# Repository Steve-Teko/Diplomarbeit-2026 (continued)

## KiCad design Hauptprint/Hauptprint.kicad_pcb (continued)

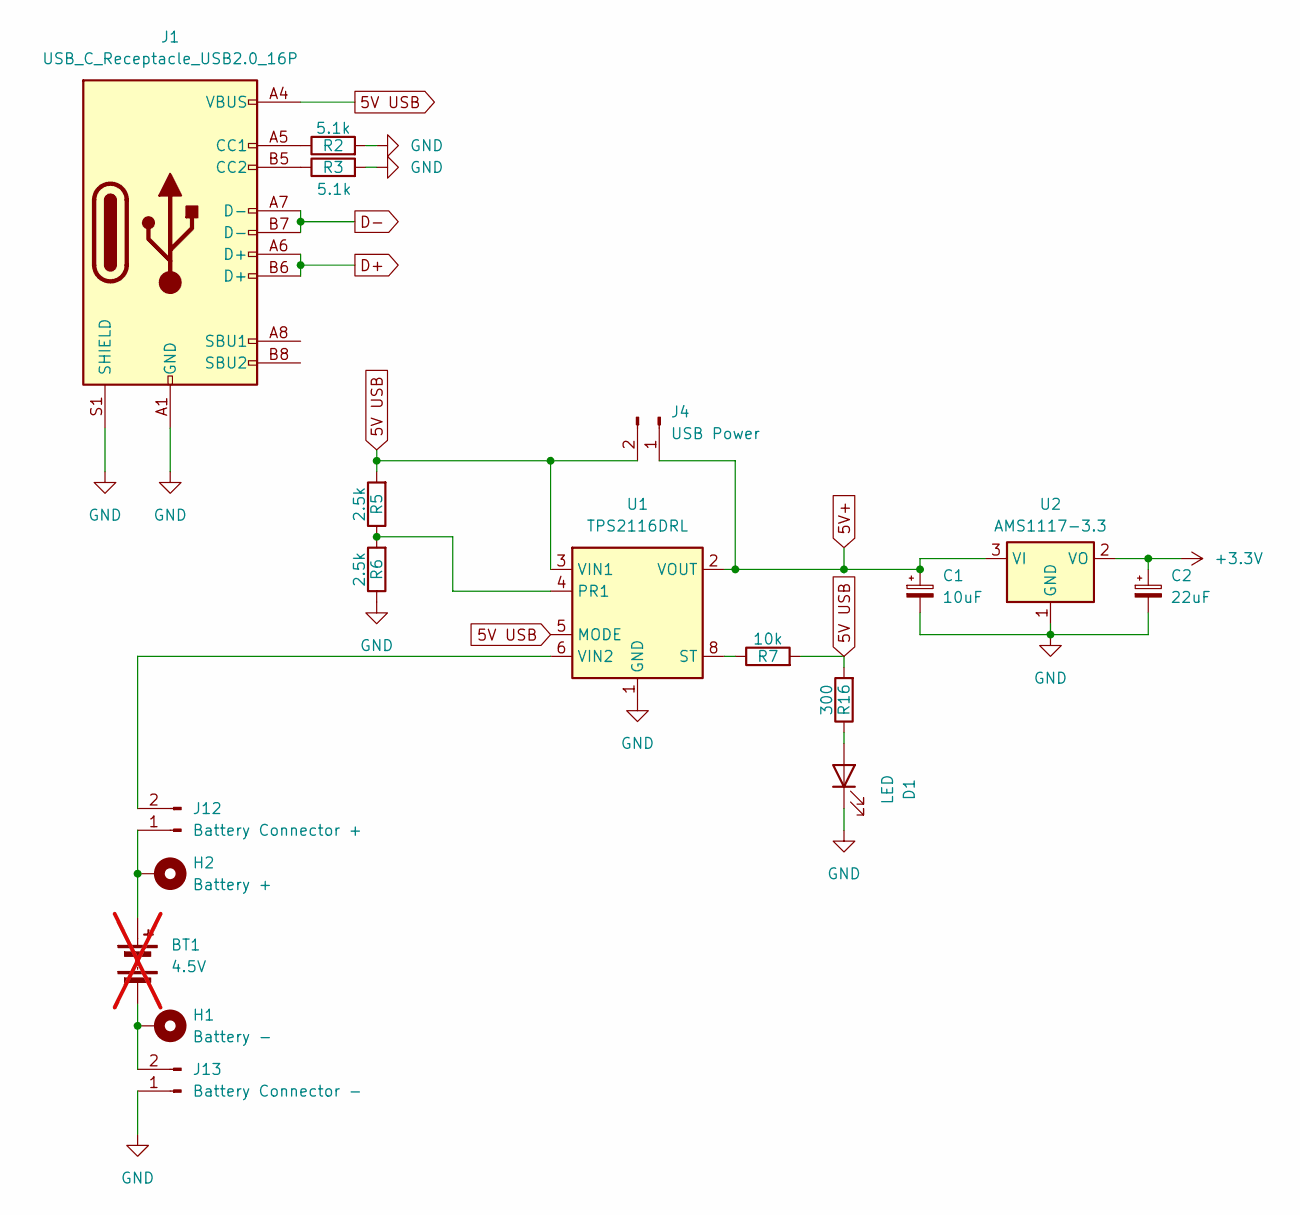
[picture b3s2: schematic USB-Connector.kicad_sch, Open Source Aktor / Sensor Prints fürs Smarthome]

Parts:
BT1: 4.5V; not fitted
C1: 10uF; CP_EIA-6032-20_AVX-F_HandSolder
C2: 22uF; CP_EIA-6032-20_AVX-F_HandSolder
D1: LED; LED_D3.0mm_Clear
H1: Battery -; MountingHole_2.2mm_M2_DIN965_Pad
H2: Battery +; MountingHole_2.2mm_M2_DIN965_Pad
J1: USB_C_Receptacle_USB2.0_16P; USB_C_Receptacle_GCT_USB4085
J4: USB Power; PinHeader_1x02_P2.54mm_Vertical
J12: Battery Connector +; PinHeader_1x02_P2.54mm_Vertical
J13: Battery Connector -; PinHeader_1x02_P2.54mm_Vertical
R2, R3: 5.1k; R_1206_3216Metric_Pad1.30x1.75mm_HandSolder
R5, R6: 2.5k; R_1206_3216Metric_Pad1.30x1.75mm_HandSolder
R7: 10k; R_1206_3216Metric_Pad1.30x1.75mm_HandSolder
R16: 300; R_Axial_DIN0207_L6.3mm_D2.5mm_P10.16mm_Horizontal
U1: TPS2116DRL; SOT-583-8
U2: AMS1117-3.3; SOT-223-3_TabPin2

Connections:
5V USB: J1.A4 (VBUS), J1.A9 (VBUS), J1.B4 (VBUS), J1.B9 (VBUS), J4.2, R5.2, R7.2, R16.2, U1.3 (VIN1), U1.5 (MODE)
5V+: C1.1, J4.1, U1.2 (VOUT), U1.7 (VOUT), U2.3 (VI); also elsewhere on the board
+3.3V: C2.1, U2.2 (VO); also elsewhere on the board
D+: J1.A6 (D+), J1.B6 (D+); also elsewhere on the board
D-: J1.A7 (D-), J1.B7 (D-); also elsewhere on the board
GND: C1.2, C2.2, D1.1 (K), J1.A1 (GND), J1.A12 (GND), J1.B1 (GND), J1.B12 (GND), J1.S1 (SHIELD), J13.1, R2.2, R3.2, R6.1, U1.1 (GND), U2.1 (GND); also elsewhere on the board
unnamed: D1.2 (A), R16.1
unnamed: J1.A5 (CC1), R2.1
unnamed: J1.B5 (CC2), R3.1
unnamed: BT1.1 (+), H2.1, J12.1
unnamed: J12.2, U1.6 (VIN2)
unnamed: BT1.2 (-), H1.1, J13.2
unnamed: R5.1, R6.2, U1.4 (PR1)
unnamed: R7.1, U1.8 (ST)

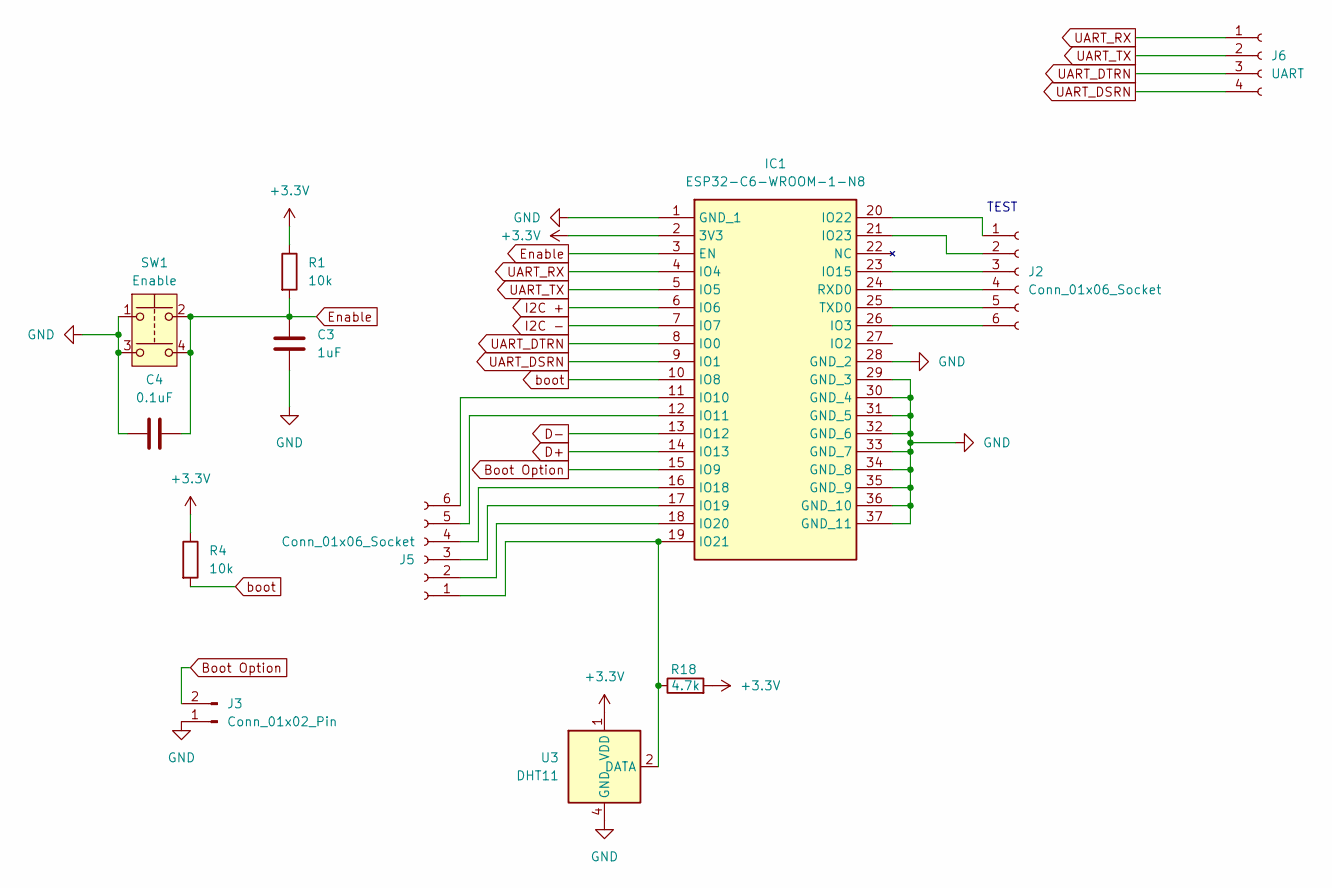
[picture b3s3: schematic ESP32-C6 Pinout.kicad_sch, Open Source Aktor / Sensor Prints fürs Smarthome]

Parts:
C3: 1uF; C_1210_3225Metric_Pad1.33x2.70mm_HandSolder
C4: 0.1uF; C_1210_3225Metric_Pad1.33x2.70mm_HandSolder
IC1: ESP32-C6-WROOM-1-N8; ESP32C6WROOM1N8; Mouser Part Number 356-ESP32C6WROOM1N8
J2, J5: Conn_01x06_Socket; PinHeader_1x06_P2.54mm_Vertical
J3: Conn_01x02_Pin; PinHeader_1x02_P2.54mm_Vertical
J6: UART; PinHeader_1x04_P2.54mm_Vertical
R1, R4: 10k; R_1206_3216Metric_Pad1.30x1.75mm_HandSolder
R18: 4.7k; R_Axial_DIN0207_L6.3mm_D2.5mm_P10.16mm_Horizontal
SW1: Enable; SW_TH_Tactile_Omron_B3F-10xx
U3: DHT11; Aosong_DHT11_5.5x12.0_P2.54mm

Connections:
+3.3V: IC1.2 (3V3), R1.1, R4.1, R18.2, U3.1 (VDD); also elsewhere on the board
Boot Option: IC1.15 (IO9), J3.2
D+: IC1.14 (IO13); also elsewhere on the board
D-: IC1.13 (IO12); also elsewhere on the board
Enable: C3.1, C4.2, IC1.3 (EN), R1.2, SW1.2, SW1.4
GND: C3.2, C4.1, IC1.1 (GND_1), IC1.28 (GND_2), IC1.29 (GND_3), IC1.30 (GND_4), IC1.31 (GND_5), IC1.32 (GND_6), IC1.33 (GND_7), IC1.34 (GND_8), IC1.35 (GND_9), IC1.36 (GND_10), IC1.37 (GND_11), J3.1, SW1.1, SW1.3, U3.4 (GND); also elsewhere on the board
I2C +: IC1.6 (IO6); also elsewhere on the board
I2C -: IC1.7 (IO7); also elsewhere on the board
unnamed: IC1.26 (IO3), J2.6
unnamed: IC1.11 (IO10), J5.6
unnamed: IC1.12 (IO11), J5.5
unnamed: IC1.23 (IO15), J2.3
unnamed: IC1.16 (IO18), J5.4
unnamed: IC1.17 (IO19), J5.3
unnamed: IC1.18 (IO20), J5.2
unnamed: IC1.19 (IO21), J5.1, R18.1, U3.2 (DATA)
unnamed: IC1.20 (IO22), J2.1
unnamed: IC1.21 (IO23), J2.2
unnamed: IC1.24 (RXD0), J2.4
unnamed: IC1.25 (TXD0), J2.5
UART_DSRN: IC1.9 (IO1), J6.4
UART_DTRN: IC1.8 (IO0), J6.3
UART_RX: IC1.4 (IO4), J6.1
UART_TX: IC1.5 (IO5), J6.2
boot: IC1.10 (IO8), R4.2

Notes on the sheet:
TEST

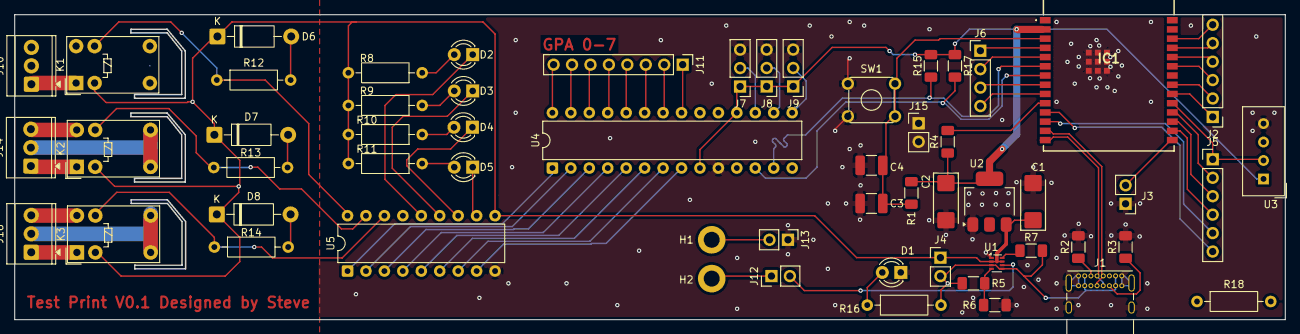
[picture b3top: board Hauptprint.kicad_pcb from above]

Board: 2 copper layers, 174.9 x 41.9 mm, 58 parts (0 on the bottom side), 77 nets.

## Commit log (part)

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2026-06-28 Create Hauptrint
    Uploading local File to Github
    Release V0.1
